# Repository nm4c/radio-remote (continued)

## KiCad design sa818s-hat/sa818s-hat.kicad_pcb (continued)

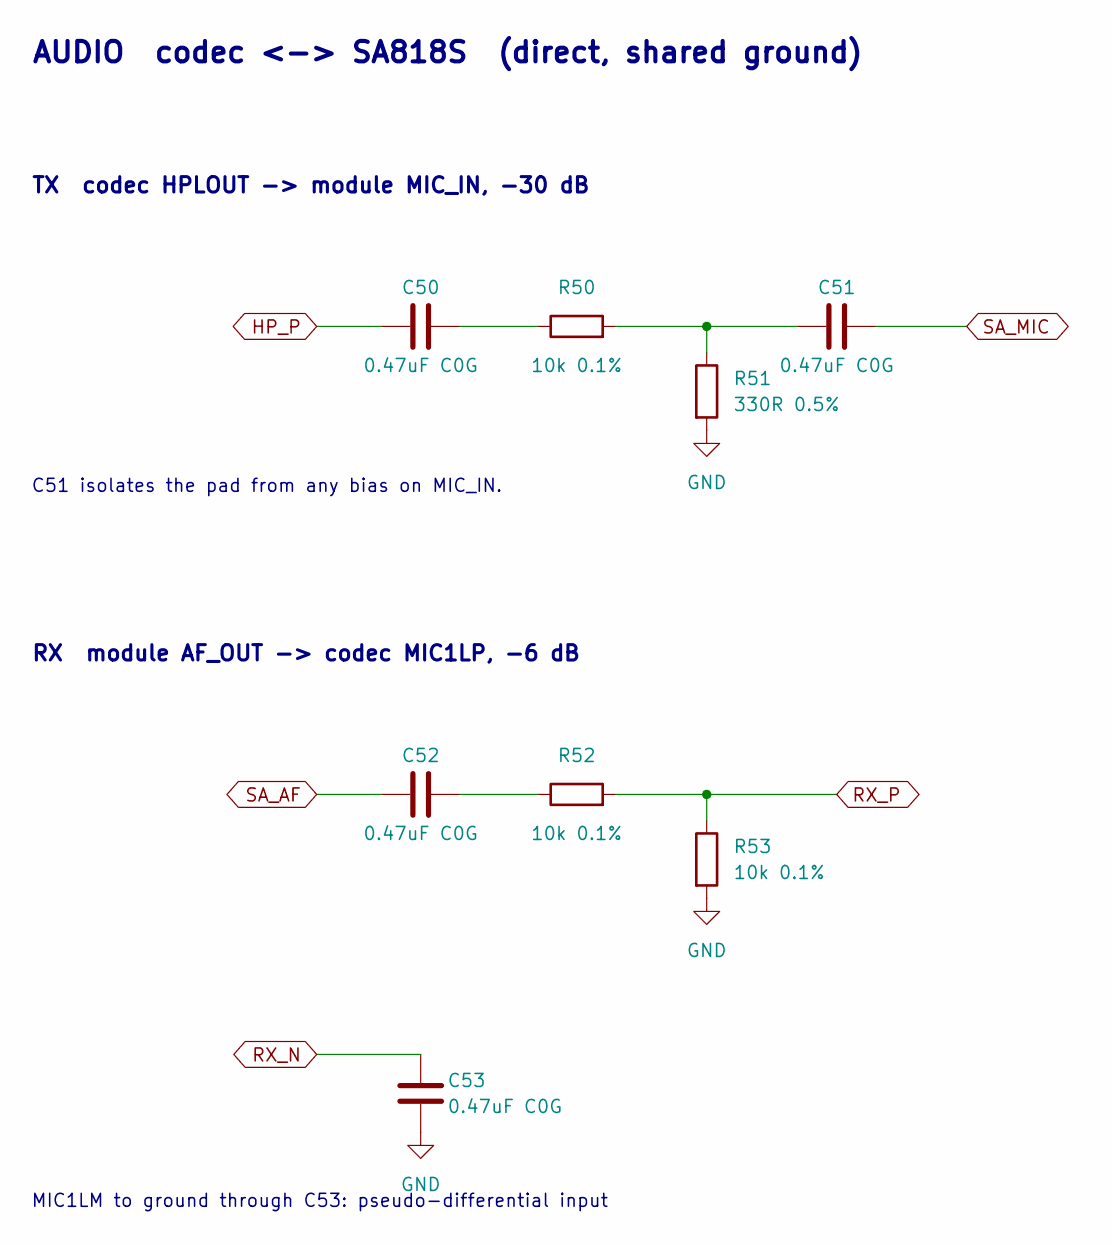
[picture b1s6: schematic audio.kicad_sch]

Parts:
C50, C51, C52, C53: 0.47uF C0G; C_1206_3216Metric; LCSC C6049896
R50, R52, R53: 10k 0.1%; R_0603_1608Metric; LCSC C95204
R51: 330R 0.5%; R_0603_1608Metric; LCSC C723588

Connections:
GND: C53.2, R51.2, R53.2; also elsewhere on the board
HP_P: C50.1; also elsewhere on the board
unnamed: C50.2, R50.1
unnamed: C51.1, R50.2, R51.1
unnamed: C52.2, R52.1
RX_N: C53.1; also elsewhere on the board
RX_P: R52.2, R53.1; also elsewhere on the board
SA_AF: C52.1; also elsewhere on the board
SA_MIC: C51.2; also elsewhere on the board

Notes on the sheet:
AUDIO codec <-> SA818S (direct, shared ground)
TX codec HPLOUT -> module MIC_IN, -30 dB
C51 isolates the pad from any bias on MIC_IN.
RX module AF_OUT -> codec MIC1LP, -6 dB
MIC1LM to ground through C53: pseudo-differential input

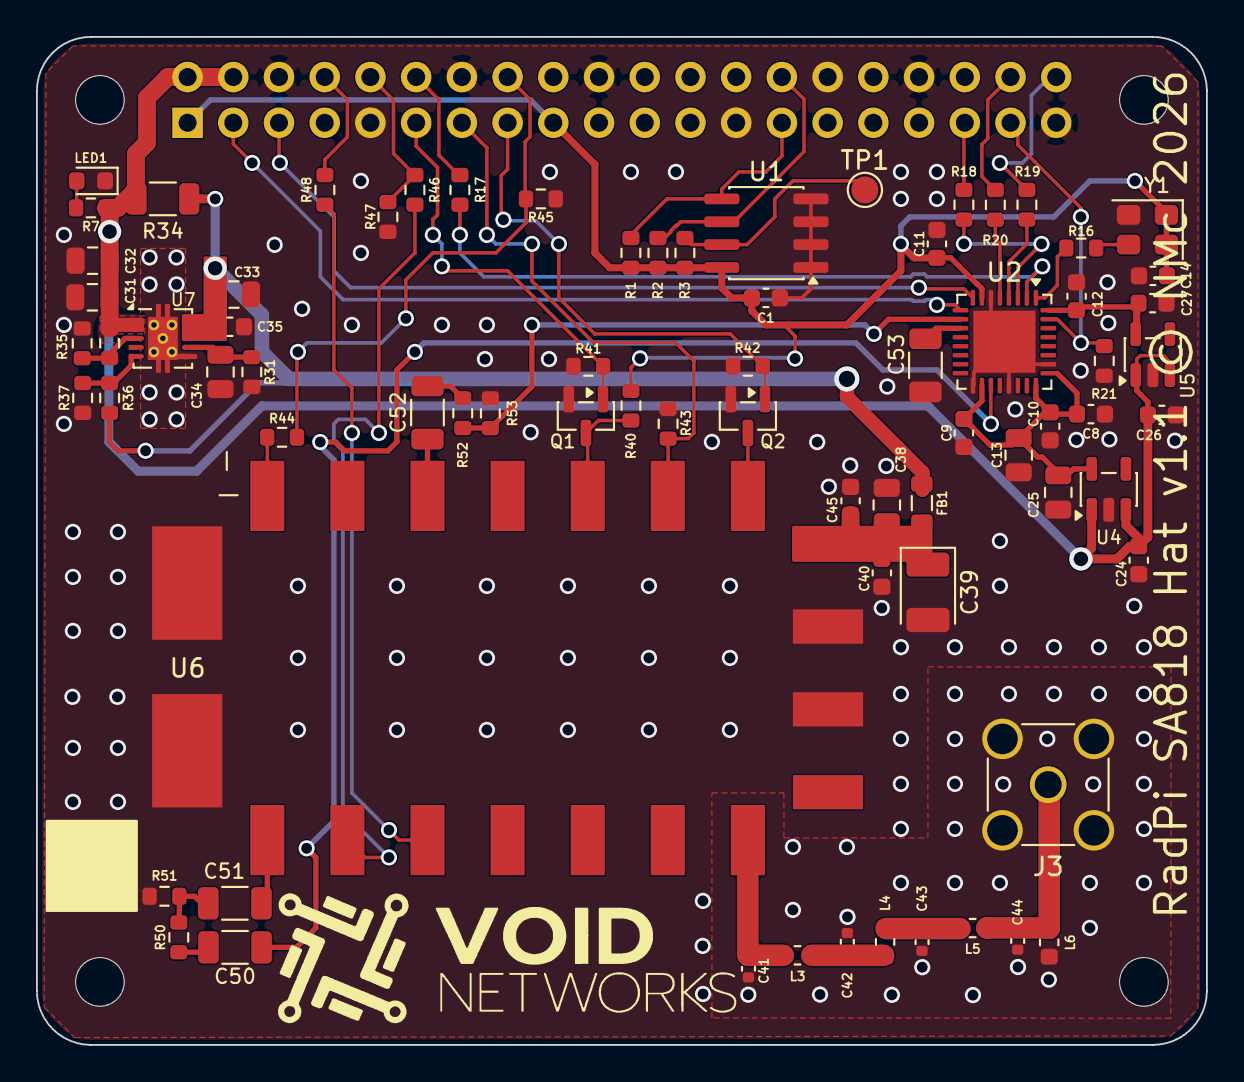
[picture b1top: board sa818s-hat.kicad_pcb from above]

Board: 2 copper layers, 65.0 x 56.0 mm, 80 parts (1 on the bottom side), 50 nets.

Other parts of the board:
MH1, MH2, MH3, MH4: MountingHole_2.7mm_M2.5

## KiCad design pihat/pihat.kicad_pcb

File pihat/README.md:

# RadPi Control HAT

A Raspberry Pi HAT that replaces the hand-wired interface in [`../docs/HARDWARE.md`](../docs/HARDWARE.md).
It has everything on one board:

- **Opto-isolated control:** PTT, channel UP/DOWN and BUSY through a TCMT4100.
- **On-board sound card:** a TLV320AIC3104 I2S codec, with isolation transformers to the radio's
  mic input and speaker.
- **Power:** a 13.8 V input with protection, and a 5 V buck that also powers the Pi.
- **HAT ID EEPROM:** tells the Pi which sound-card overlay to load at boot.

| File | What it is |
|---|---|
| `pihat.kicad_pro` / `.kicad_sch` / `.kicad_pcb` | KiCad project |
| [`docs/schematic/radpi-control-hat.html`](docs/schematic/radpi-control-hat.html) | Reference schematic: 7 sheets, netlist, parts, pre-layout checks. Open it in a browser. |
| [`docs/BOM.md`](docs/BOM.md) | BoM notes and cost summary |
| [`docs/jlc-bom.csv`](docs/jlc-bom.csv) | JLCPCB assembly BoM |
| `docs/schematic/gen.py` | Regenerates the schematic page and the CSV from one parts list |
| [`docs/schematic.svg`](docs/schematic.svg) | The KiCad schematic, all sheets on one page (made by `tools/kicad/overview.py`) |

## Schematic

The whole circuit on one page, straight from the KiCad schematic (click to open it full size; part
and net names are searchable). Labels with the same name are connected. Regenerate it with
`python3 tools/kicad/overview.py` after changing the schematic.

## Software

The codec uses the `tlv320aic3x` driver already in Raspberry Pi OS, with a small custom overlay
(still to write): `simple-audio-card` with the codec at I2C 0x18, `reset-gpios` on GPIO26 (active
low) and a fixed 12 MHz system clock. `simple-audio-card` always clocks the codec from MCLK, which
is where Y1's 12 MHz goes on this board. Don't use the stock `dacberry400` overlay: its driver
clocks the codec's PLL from BCLK while telling it the clock is 12 MHz, so the sample rate would be
wrong here. In ALSA, set the HPLCOM output to "differential of HPLOUT" so T1 is driven
differentially. After that the remote-head server sees an ordinary ALSA sound card: set
`audio.input_device` / `output_device` in `config.yaml` to its name, and `gpio.busy_pin: 23` with
`busy_pull_up: true`.

**Powering:** the HAT powers the Pi through header pins 2 and 4. Don't power the Pi from its USB-C
socket while the HAT is fitted and its 13.8 V input is off: the Pi's 5 V would then sit on the
buck's output with no input, which the LMR33640 datasheet says not to allow.

## Licence

The hardware design in this folder is licensed under the **CERN Open Hardware Licence v2, Strongly
Reciprocal (CERN-OHL-S-2.0)**. See [`LICENSE`](LICENSE). The generator scripts in `tools/` and
`docs/schematic/gen.py` are software and are GPL-3.0-or-later (see the repository root).

CERN-OHL-S asks that products made from the design say where the source can be found. Put this on
the board's silkscreen during layout, for example:

    RadPi Control HAT  CERN-OHL-S-2.0  github.com/nm4c/radpi

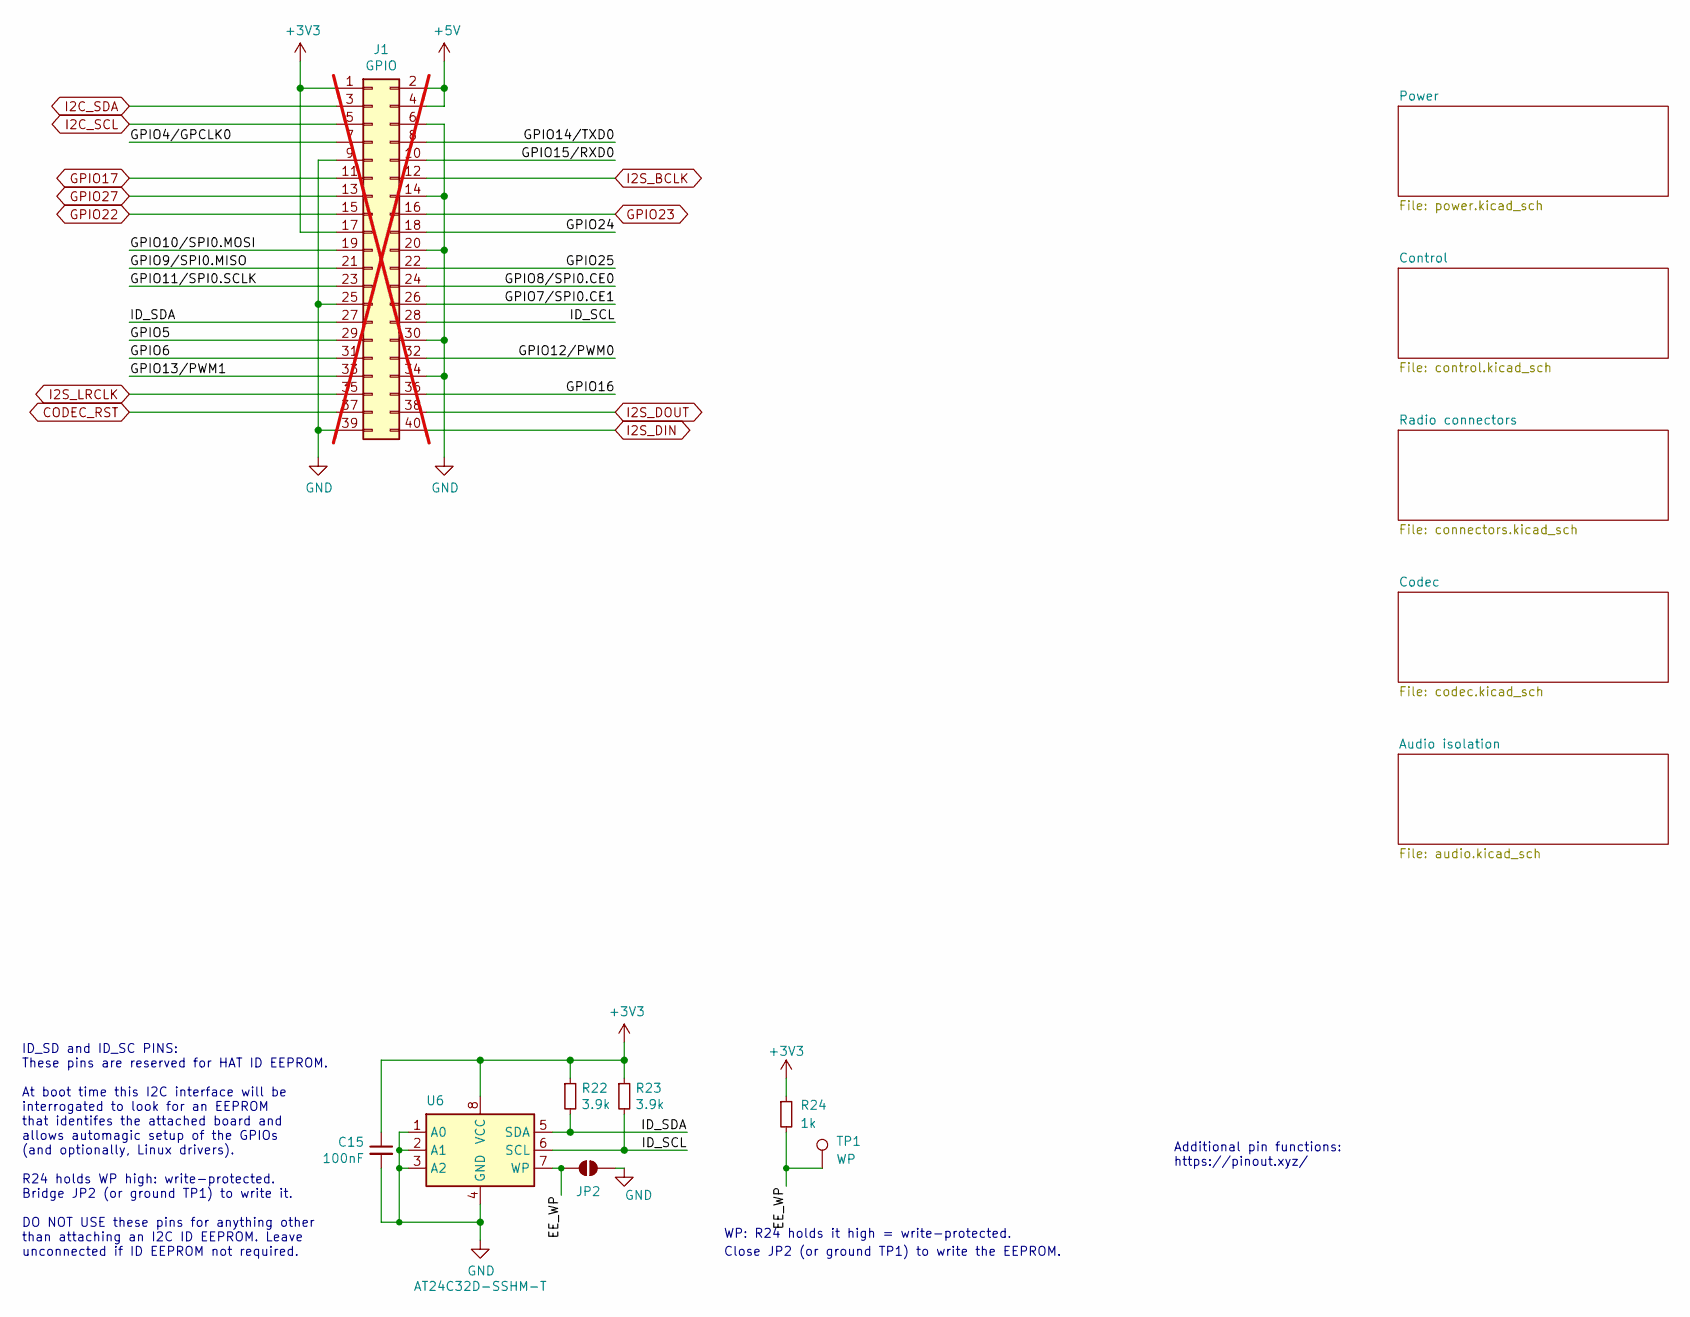
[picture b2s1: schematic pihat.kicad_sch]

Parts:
C15: 100nF; C_0603_1608Metric; LCSC C14663
J1: GPIO; PinSocket_2x20_P2.54mm_Vertical; LCSC C2977589; not fitted
JP2: WP write enable; SolderJumper-2_P1.3mm_Open_RoundedPad1.0x1.5mm
R22, R23: 3.9k; R_0603_1608Metric; LCSC C23018
R24: 1k; R_0603_1608Metric; LCSC C21190
TP1: WP; TestPoint_Pad_D1.5mm
U6: AT24C32D-SSHM-T; SOIC-8_3.9x4.9mm_P1.27mm; LCSC C60583

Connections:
+3V3: C15.1, J1.1, J1.17, R22.1, R23.1, R24.1, U6.8 (VCC); also elsewhere on the board
+5V: J1.2, J1.4; also elsewhere on the board
/EE_WP: JP2.1 (A), R24.2, TP1.1 (1_1), U6.7 (WP)
/GPIO4/GPCLK0: J1.7
/GPIO5: J1.29
/GPIO6: J1.31
/GPIO7/SPI0.CE1: J1.26
/GPIO8/SPI0.CE0: J1.24
/GPIO9/SPI0.MISO: J1.21
/GPIO10/SPI0.MOSI: J1.19
/GPIO11/SPI0.SCLK: J1.23
/GPIO12/PWM0: J1.32
/GPIO13/PWM1: J1.33
/GPIO14/TXD0: J1.8
/GPIO15/RXD0: J1.10
/GPIO16: J1.36
/GPIO24: J1.18
/GPIO25: J1.22
/ID_SCL: J1.28, R23.2, U6.6 (SCL)
/ID_SDA: J1.27, R22.2, U6.5 (SDA)
CODEC_RST: J1.37; also elsewhere on the board
GND: C15.2, J1.6, J1.9, J1.14, J1.20, J1.25, J1.30, J1.34, J1.39, JP2.2 (B), U6.1 (A0), U6.2 (A1), U6.3 (A2), U6.4 (GND); also elsewhere on the board
GPIO17: J1.11; also elsewhere on the board
GPIO22: J1.15; also elsewhere on the board
GPIO23: J1.16; also elsewhere on the board
GPIO27: J1.13; also elsewhere on the board
I2C_SCL: J1.5; also elsewhere on the board
I2C_SDA: J1.3; also elsewhere on the board
I2S_BCLK: J1.12; also elsewhere on the board
I2S_DIN: J1.40; also elsewhere on the board
I2S_DOUT: J1.38; also elsewhere on the board
I2S_LRCLK: J1.35; also elsewhere on the board

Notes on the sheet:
Additional pin functions: https://pinout.xyz/
ID_SD and ID_SC PINS: These pins are reserved for HAT ID EEPROM. At boot time this I2C interface will be interrogated to look for an EEPROM that identifes the attached board and allows automagic setup of the GPIOs (and optionally, Linux drivers). R24 holds WP high: write-protected. Bridge JP2 (or g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
WP: R24 holds it high = write-protected.
Close JP2 (or ground TP1) to write the EEPROM.

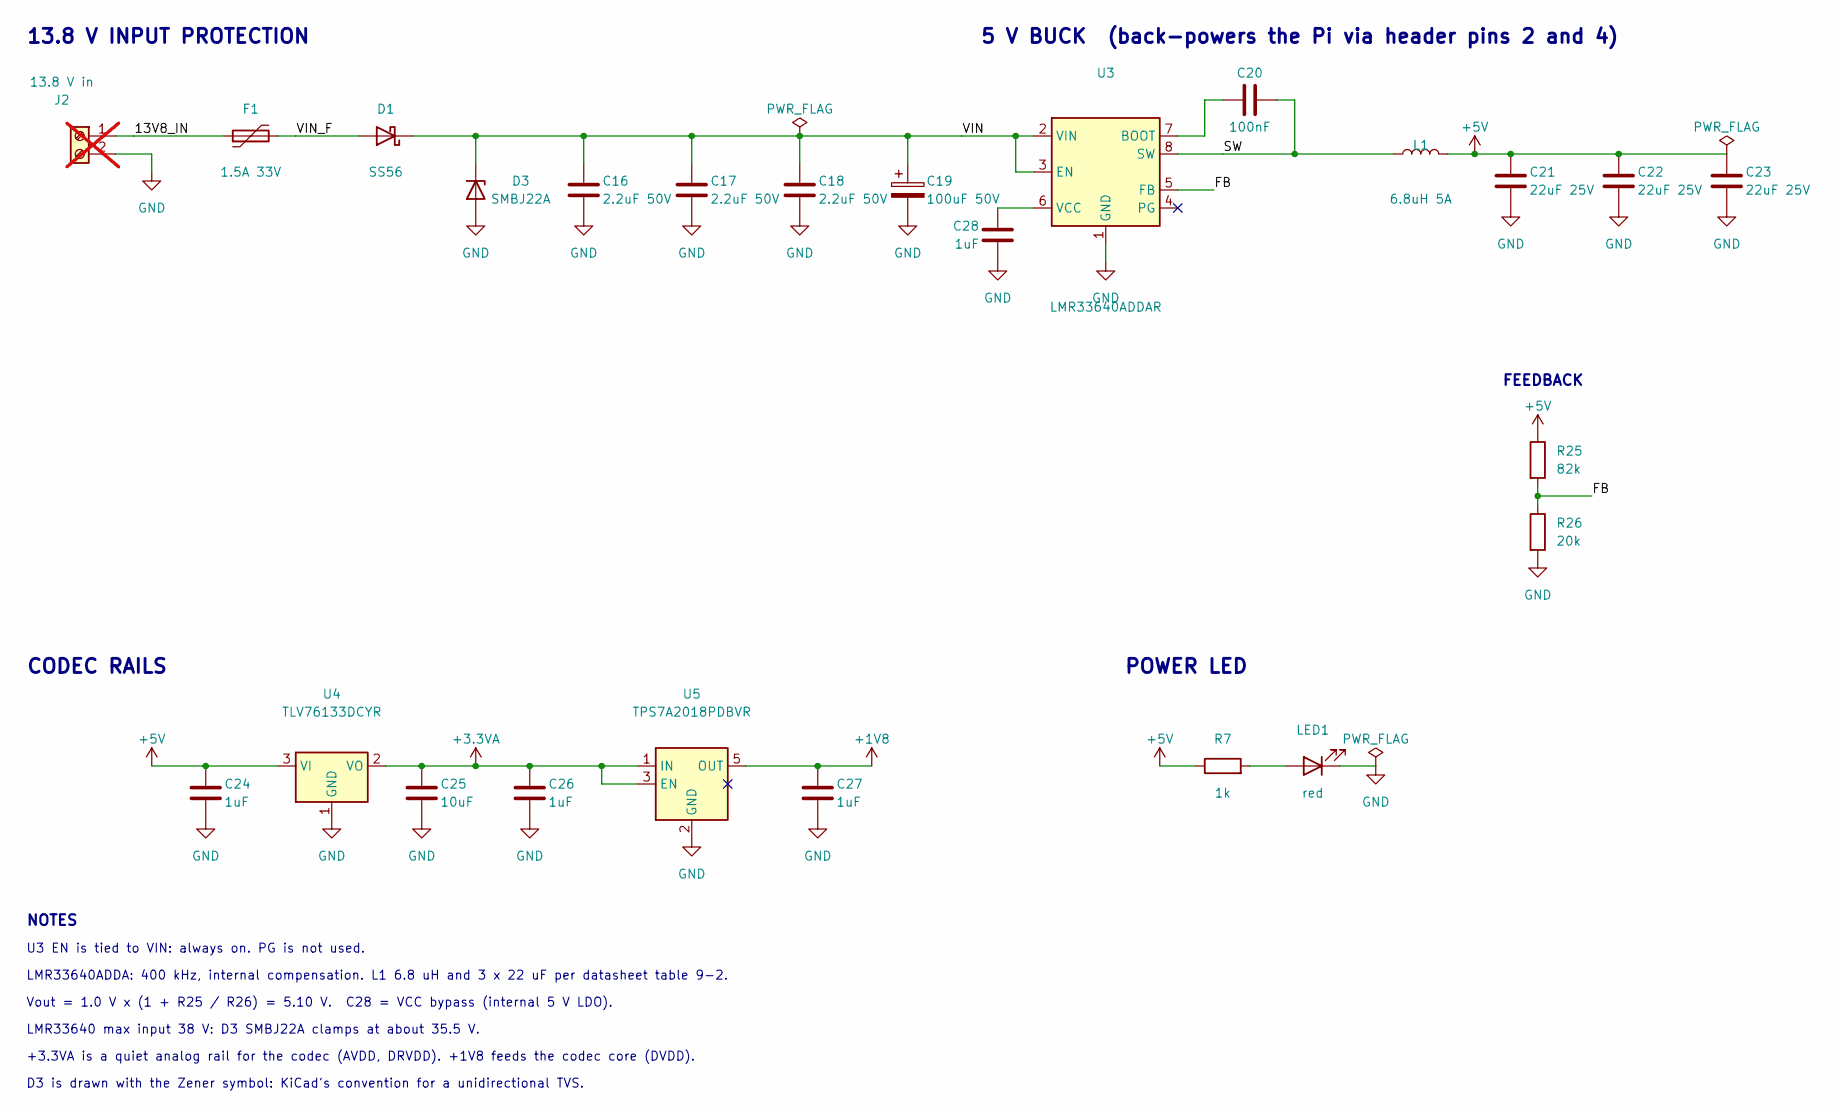
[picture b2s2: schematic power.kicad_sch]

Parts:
C16, C17, C18: 2.2uF 50V; C_1206_3216Metric; LCSC C50254
C19: 100uF 50V; CP_Elec_8x10.5; LCSC C72480
C20: 100nF; C_0603_1608Metric; LCSC C14663
C21, C22, C23: 22uF 25V; C_1206_3216Metric; LCSC C12891
C24, C26, C27, C28: 1uF; C_0603_1608Metric; LCSC C15849
C25: 10uF; C_0805_2012Metric; LCSC C15850
D1: SS56; D_SMA; LCSC C65009
D3: SMBJ22A; D_SMB; LCSC C224015
F1: 1.5A 33V; Fuse_1812_4532Metric; LCSC C18198333
J2: 13.8 V in; Xinlaiya_XY2500V-F-3.5_1x02_P3.50mm_Vertical; LCSC C880554; not fitted
L1: 6.8uH 5A; L_Changjiang_FXL0630; LCSC C167221
LED1: red; LED_0603_1608Metric; LCSC C2286
R7: 1k; R_0603_1608Metric; LCSC C21190
R25: 82k; R_0603_1608Metric; LCSC C23254
R26: 20k; R_0603_1608Metric; LCSC C4184
U3: LMR33640ADDAR; Texas_HSOP-8-1EP_3.9x4.9mm_P1.27mm_ThermalVias; LCSC C2836966
U4: TLV76133DCYR; SOT-223-3_TabPin2; LCSC C7527500
U5: TPS7A2018PDBVR; SOT-23-5; LCSC C963430

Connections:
+1V8: C27.1, U5.5 (OUT); also elsewhere on the board
+3.3VA: C25.1, C26.1, U4.2 (VO), U5.1 (IN), U5.3 (EN); also elsewhere on the board
+5V: C21.1, C22.1, C23.1, C24.1, L1.2, R7.1, R25.1, U4.3 (VI); also elsewhere on the board
/Power/13V8_IN: F1.1, J2.1
/Power/FB: R25.2, R26.1, U3.5 (FB)
/Power/SW: C20.2, L1.1, U3.8 (SW)
/Power/VIN: C16.1, C17.1, C18.1, C19.1, D1.1 (K), D3.1 (K), U3.2 (VIN), U3.3 (EN)
/Power/VIN_F: D1.2 (A), F1.2
GND: C16.2, C17.2, C18.2, C19.2, C21.2, C22.2, C23.2, C24.2, C25.2, C26.2, C27.2, C28.2, D3.2 (A), J2.2, LED1.1 (K), R26.2, U3.1 (GND), U3.9 (GND), U4.1 (GND), U5.2 (GND); also elsewhere on the board
unnamed: LED1.2 (A), R7.2
unnamed: C20.1, U3.7 (BOOT)
unnamed: C28.1, U3.6 (VCC)

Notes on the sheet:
13.8 V INPUT PROTECTION
5 V BUCK (back-powers the Pi via header pins 2 and 4)
FEEDBACK
CODEC RAILS
POWER LED
NOTES
U3 EN is tied to VIN: always on. PG is not used.
LMR33640ADDA: 400 kHz, internal compensation. L1 6.8 uH and 3 x 22 uF per datasheet table 9-2.
Vout = 1.0 V x (1 + R25 / R26) = 5.10 V. C28 = VCC bypass (internal 5 V LDO).
LMR33640 max input 38 V: D3 SMBJ22A clamps at about 35.5 V.
+3.3VA is a quiet analog rail for the codec (AVDD, DRVDD). +1V8 feeds the codec core (DVDD).
D3 is drawn with the Zener symbol: KiCad's convention for a unidirectional TVS.

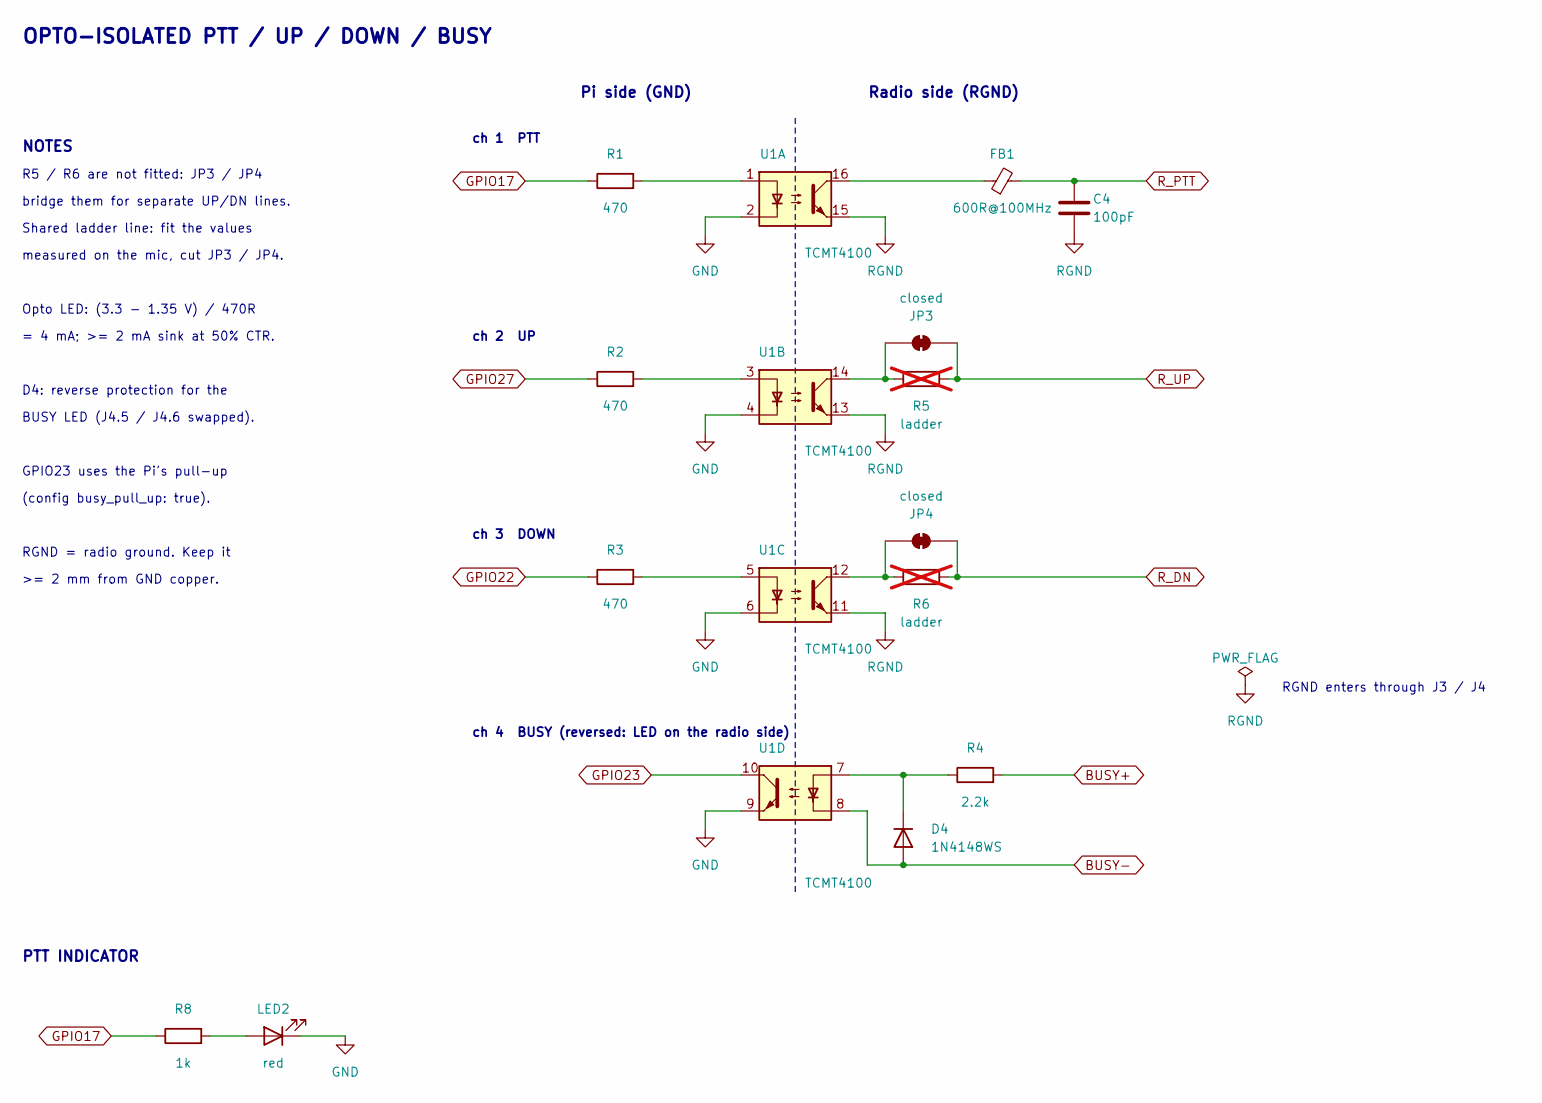
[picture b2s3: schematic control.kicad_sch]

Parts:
C4: 100pF; C_0603_1608Metric; LCSC C14858
D4: 1N4148WS; D_SOD-323; LCSC C2128
FB1: 600R@100MHz; L_0603_1608Metric; LCSC C1002
JP3, JP4: closed; SolderJumper-2_P1.3mm_Bridged_RoundedPad1.0x1.5mm
LED2: red; LED_0603_1608Metric; LCSC C2286
R1, R2, R3: 470; R_0603_1608Metric; LCSC C23179
R4: 2.2k; R_0603_1608Metric; LCSC C4190
R5, R6: ladder; R_0603_1608Metric; not fitted
R8: 1k; R_0603_1608Metric; LCSC C21190
U1: TCMT4100; SOP-16_4.4x10.4mm_P1.27mm; LCSC C2938669

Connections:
BUSY+: R4.2; also elsewhere on the board
BUSY-: D4.2 (A), U1.8; also elsewhere on the board
GND: LED2.1 (K), U1.2, U1.4, U1.6, U1.9; also elsewhere on the board
GPIO17: R1.1, R8.1; also elsewhere on the board
GPIO22: R3.1; also elsewhere on the board
GPIO23: U1.10; also elsewhere on the board
GPIO27: R2.1; also elsewhere on the board
unnamed: D4.1 (K), R4.1, U1.7
unnamed: FB1.1, U1.16
unnamed: JP3.1 (A), R5.1, U1.14
unnamed: JP4.1 (A), R6.1, U1.12
unnamed: LED2.2 (A), R8.2
unnamed: R1.2, U1.1
unnamed: R2.2, U1.3
unnamed: R3.2, U1.5
RGND: C4.2, U1.11, U1.13, U1.15; also elsewhere on the board
R_DN: JP4.2 (B), R6.2; also elsewhere on the board
R_PTT: C4.1, FB1.2; also elsewhere on the board
R_UP: JP3.2 (B), R5.2; also elsewhere on the board

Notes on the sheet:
OPTO-ISOLATED PTT / UP / DOWN / BUSY
Pi side (GND)
Radio side (RGND)
ch 1 PTT
ch 2 UP
ch 3 DOWN
ch 4 BUSY (reversed: LED on the radio side)
RGND enters through J3 / J4
PTT INDICATOR
NOTES
R5 / R6 are not fitted: JP3 / JP4
bridge them for separate UP/DN lines.
Shared ladder line: fit the values
measured on the mic, cut JP3 / JP4.
Opto LED: (3.3 - 1.35 V) / 470R
= 4 mA; >= 2 mA sink at 50% CTR.
D4: reverse protection for the
BUSY LED (J4.5 / J4.6 swapped).
GPIO23 uses the Pi's pull-up
(config busy_pull_up: true).
RGND = radio ground. Keep it
>= 2 mm from GND copper.

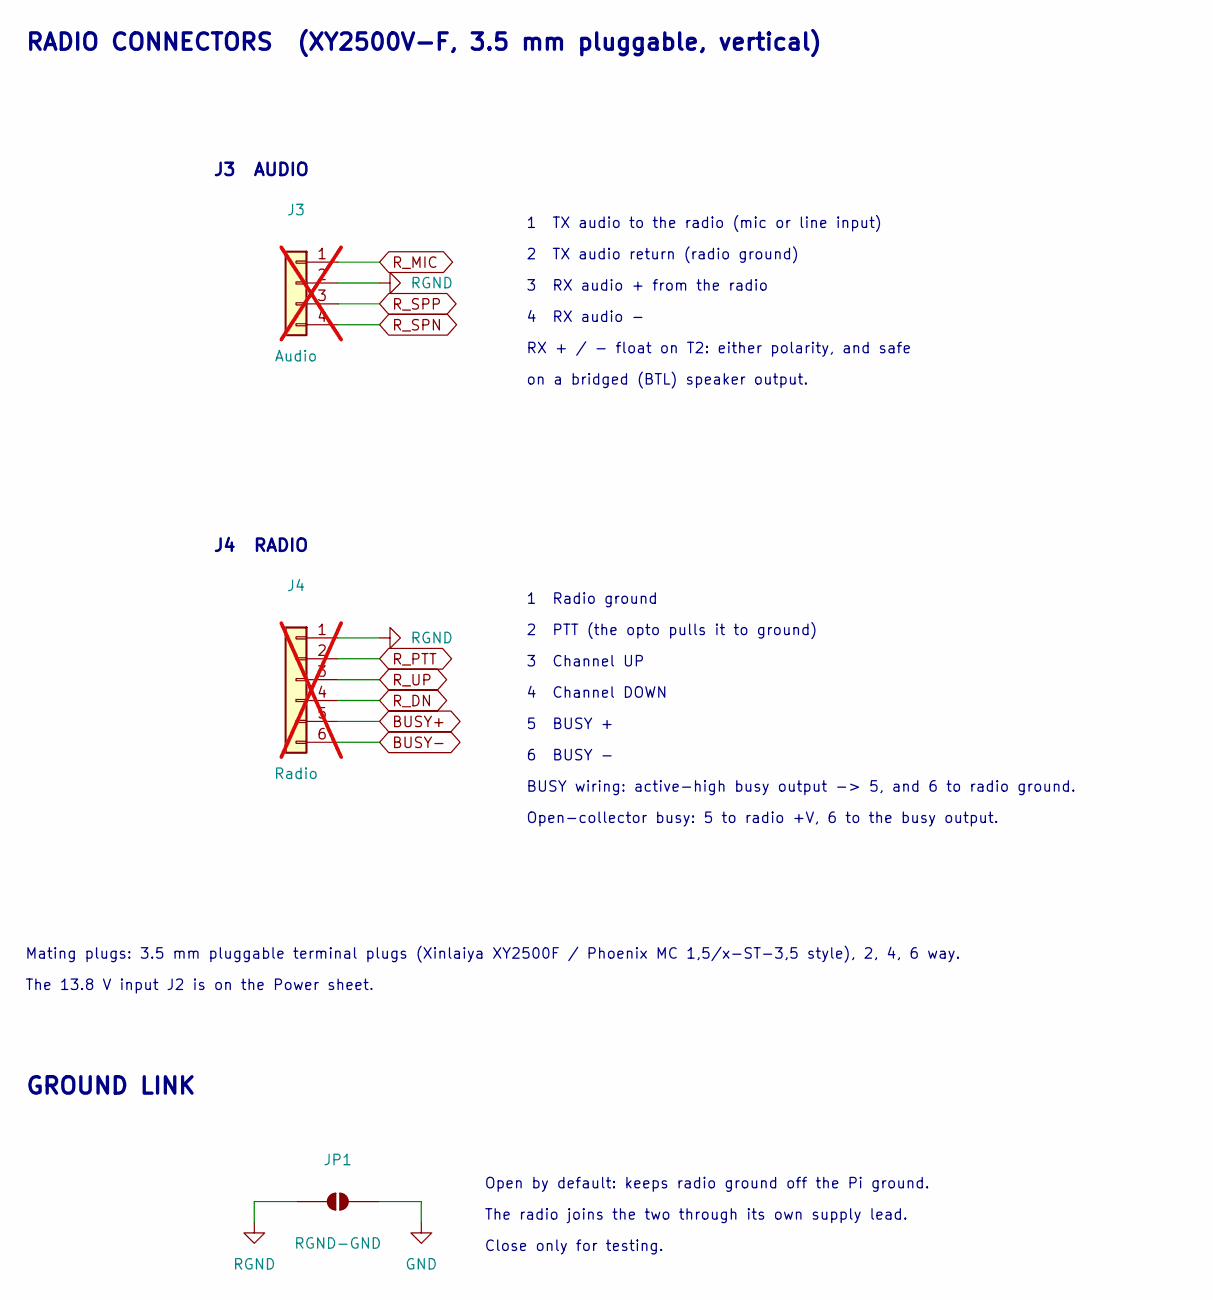
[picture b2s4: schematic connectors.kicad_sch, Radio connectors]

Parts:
J3: Audio; Xinlaiya_XY2500V-F-3.5_1x04_P3.50mm_Vertical; LCSC C880556; not fitted
J4: Radio; Xinlaiya_XY2500V-F-3.5_1x06_P3.50mm_Vertical; LCSC C880558; not fitted
JP1: RGND-GND; SolderJumper-2_P1.3mm_Open_RoundedPad1.0x1.5mm

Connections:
BUSY+: J4.5; also elsewhere on the board
BUSY-: J4.6; also elsewhere on the board
GND: JP1.2 (B); also elsewhere on the board
RGND: J3.2, J4.1, JP1.1 (A); also elsewhere on the board
R_DN: J4.4; also elsewhere on the board
R_MIC: J3.1; also elsewhere on the board
R_PTT: J4.2; also elsewhere on the board
R_SPN: J3.4; also elsewhere on the board
R_SPP: J3.3; also elsewhere on the board
R_UP: J4.3; also elsewhere on the board

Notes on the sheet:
RADIO CONNECTORS (XY2500V-F, 3.5 mm pluggable, vertical)
J3 AUDIO
1 TX audio to the radio (mic or line input)
2 TX audio return (radio ground)
3 RX audio + from the radio
4 RX audio -
RX + / - float on T2: either polarity, and safe
on a bridged (BTL) speaker output.
J4 RADIO
1 Radio ground
2 PTT (the opto pulls it to ground)
3 Channel UP
4 Channel DOWN
5 BUSY +
6 BUSY -
BUSY wiring: active-high busy output -> 5, and 6 to radio ground.
Open-collector busy: 5 to radio +V, 6 to the busy output.
Mating plugs: 3.5 mm pluggable terminal plugs (Xinlaiya XY2500F / Phoenix MC 1,5/x-ST-3,5 style), 2, 4, 6 way.
The 13.8 V input J2 is on the Power sheet.
GROUND LINK
Open by default: keeps radio ground off the Pi ground.
The radio joins the two through its own supply lead.
Close only for testing.

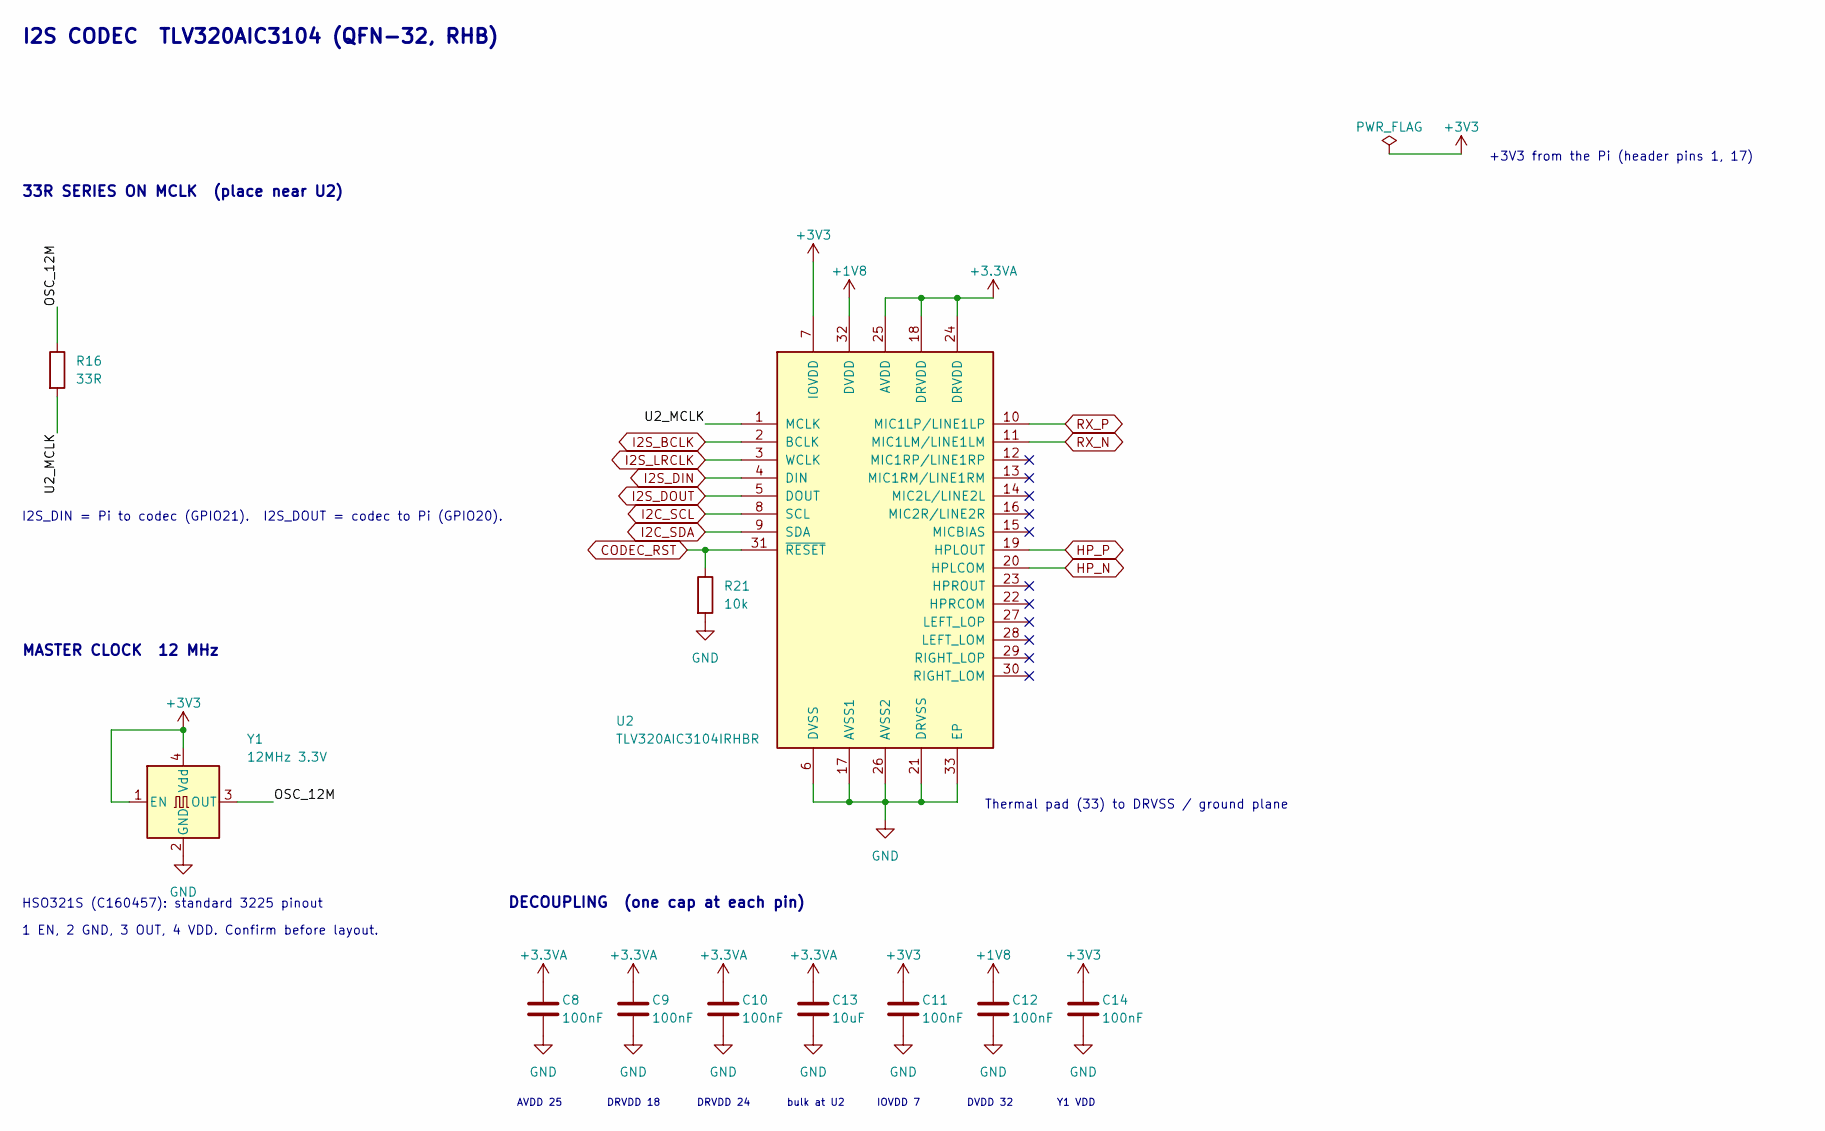
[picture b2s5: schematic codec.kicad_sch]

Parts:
C8, C9, C10, C11, C12, C14: 100nF; C_0603_1608Metric; LCSC C14663
C13: 10uF; C_0805_2012Metric; LCSC C15850
R16: 33R; R_0603_1608Metric; LCSC C23140
R21: 10k; R_0603_1608Metric; LCSC C25804
U2: TLV320AIC3104IRHBR; QFN-32-1EP_5x5mm_P0.5mm_EP3.45x3.45mm; LCSC C181753
Y1: 12MHz 3.3V; Oscillator_SMD_Abracon_ASE-4Pin_3.2x2.5mm; LCSC C160457

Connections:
+1V8: C12.1, U2.32 (DVDD); also elsewhere on the board
+3.3VA: C8.1, C9.1, C10.1, C13.1, U2.18 (DRVDD), U2.24 (DRVDD), U2.25 (AVDD); also elsewhere on the board
+3V3: C11.1, C14.1, U2.7 (IOVDD), Y1.1 (EN), Y1.4 (Vdd); also elsewhere on the board
/Codec/OSC_12M: R16.1, Y1.3 (OUT)
/Codec/U2_MCLK: R16.2, U2.1 (MCLK)
CODEC_RST: R21.1, U2.31 (~RESET); also elsewhere on the board
GND: C8.2, C9.2, C10.2, C11.2, C12.2, C13.2, C14.2, R21.2, U2.6 (DVSS), U2.17 (AVSS1), U2.21 (DRVSS), U2.26 (AVSS2), U2.33 (EP), Y1.2 (GND); also elsewhere on the board
HP_N: U2.20 (HPLCOM); also elsewhere on the board
HP_P: U2.19 (HPLOUT); also elsewhere on the board
I2C_SCL: U2.8 (SCL); also elsewhere on the board
I2C_SDA: U2.9 (SDA); also elsewhere on the board
I2S_BCLK: U2.2 (BCLK); also elsewhere on the board
I2S_DIN: U2.4 (DIN); also elsewhere on the board
I2S_DOUT: U2.5 (DOUT); also elsewhere on the board
I2S_LRCLK: U2.3 (WCLK); also elsewhere on the board
RX_N: U2.11 (MIC1LM/LINE1LM); also elsewhere on the board
RX_P: U2.10 (MIC1LP/LINE1LP); also elsewhere on the board

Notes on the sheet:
I2S CODEC TLV320AIC3104 (QFN-32, RHB)
Thermal pad (33) to DRVSS / ground plane
33R SERIES ON MCLK (place near U2)
I2S_DIN = Pi to codec (GPIO21). I2S_DOUT = codec to Pi (GPIO20).
MASTER CLOCK 12 MHz
HSO321S (C160457): standard 3225 pinout
1 EN, 2 GND, 3 OUT, 4 VDD. Confirm before layout.
DECOUPLING (one cap at each pin)
AVDD 25
DRVDD 18
DRVDD 24
bulk at U2
IOVDD 7
DVDD 32
Y1 VDD
+3V3 from the Pi (header pins 1, 17)

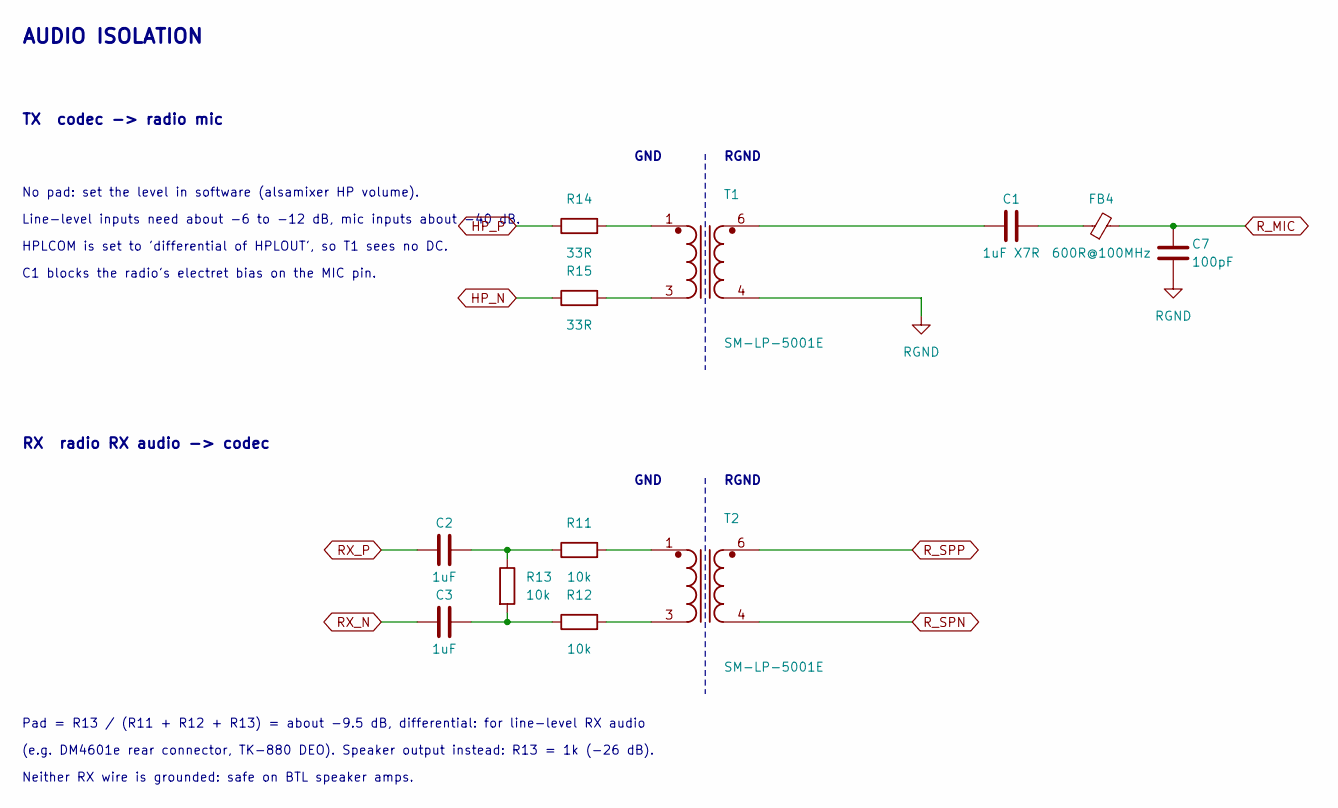
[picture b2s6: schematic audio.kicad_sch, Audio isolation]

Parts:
C1: 1uF X7R; C_0805_2012Metric; LCSC C28323
C2, C3: 1uF; C_0603_1608Metric; LCSC C15849
C7: 100pF; C_0603_1608Metric; LCSC C14858
FB4: 600R@100MHz; L_0603_1608Metric; LCSC C1002
R11, R12, R13: 10k; R_0603_1608Metric; LCSC C25804
R14, R15: 33R; R_0603_1608Metric; LCSC C23140
T1, T2: SM-LP-5001E; Bourns_SM-LP-5001; LCSC C840532

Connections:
HP_N: R15.1; also elsewhere on the board
HP_P: R14.1; also elsewhere on the board
unnamed: C1.1, T1.6
unnamed: C1.2, FB4.1
unnamed: C2.2, R11.1, R13.1
unnamed: C3.2, R12.1, R13.2
unnamed: R11.2, T2.1
unnamed: R12.2, T2.3
unnamed: R14.2, T1.1
unnamed: R15.2, T1.3
RGND: C7.2, T1.4; also elsewhere on the board
RX_N: C3.1; also elsewhere on the board
RX_P: C2.1; also elsewhere on the board
R_MIC: C7.1, FB4.2; also elsewhere on the board
R_SPN: T2.4; also elsewhere on the board
R_SPP: T2.6; also elsewhere on the board

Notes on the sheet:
AUDIO ISOLATION
TX codec -> radio mic
GND
RGND
No pad: set the level in software (alsamixer HP volume).
Line-level inputs need about -6 to -12 dB, mic inputs about -40 dB.
HPLCOM is set to 'differential of HPLOUT', so T1 sees no DC.
C1 blocks the radio's electret bias on the MIC pin.
RX radio RX audio -> codec
Pad = R13 / (R11 + R12 + R13) = about -9.5 dB, differential: for line-level RX audio
(e.g. DM4601e rear connector, TK-880 DEO). Speaker output instead: R13 = 1k (-26 dB).
Neither RX wire is grounded: safe on BTL speaker amps.

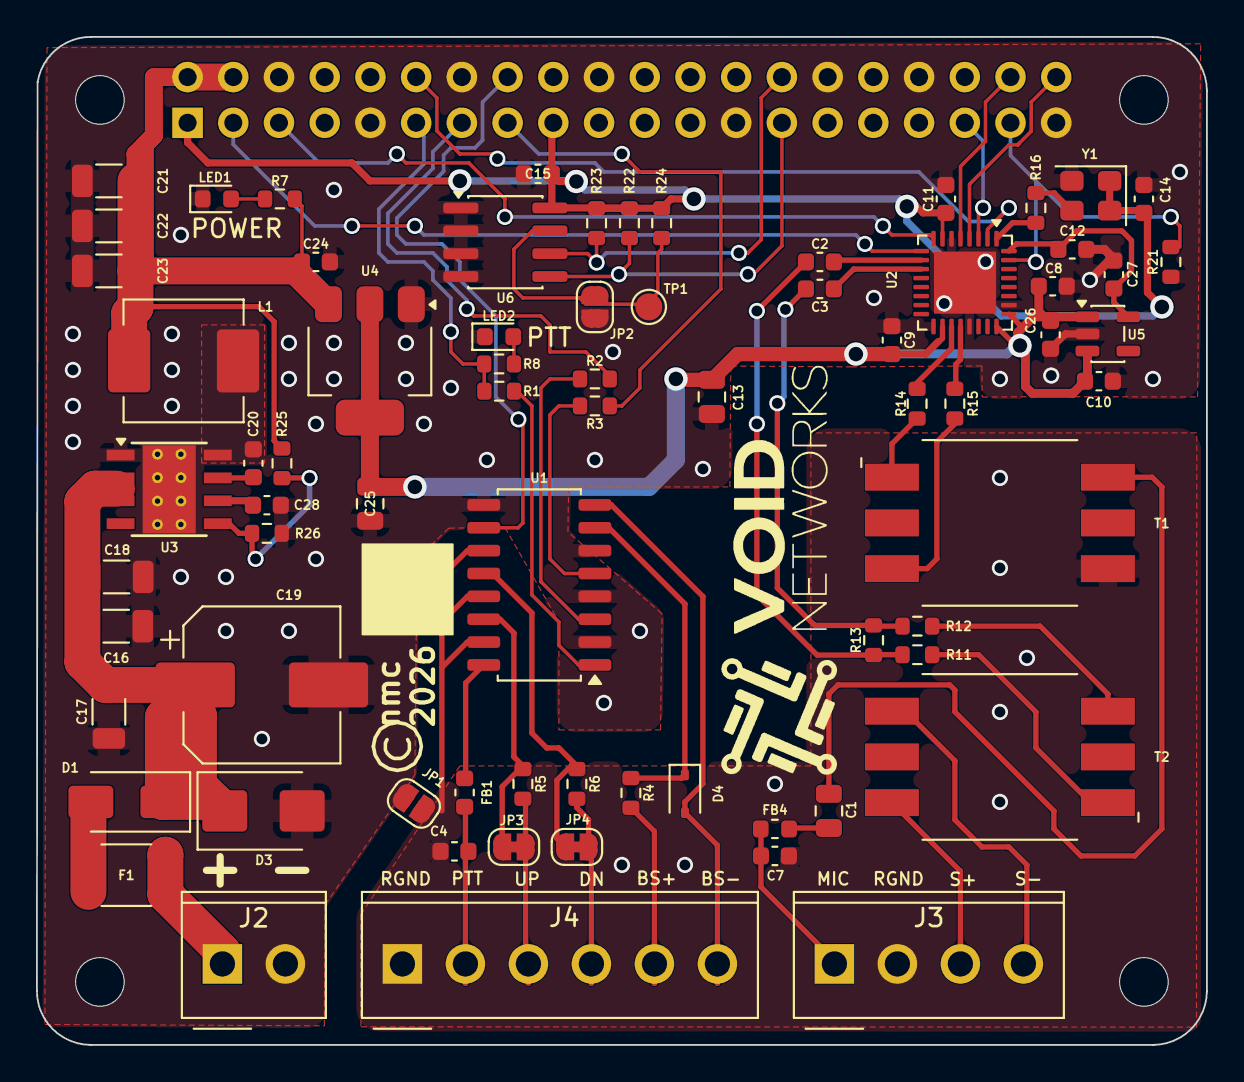
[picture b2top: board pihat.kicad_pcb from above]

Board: 2 copper layers, 65.0 x 56.0 mm, 77 parts (1 on the bottom side), 58 nets.

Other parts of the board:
MH1, MH2, MH3, MH4: MountingHole_2.7mm_M2.5

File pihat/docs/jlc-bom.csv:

Comment,Designator,Footprint,LCSC Part #
TCMT4100 quad opto,U1,SOIC-16_4.4x10.3mm_P1.27mm,C2938669
TLV320AIC3104IRHBR codec,U2,QFN-32-1EP_5x5mm_P0.5mm,C181753
LMR33640ADDAR buck,U3,HSOP-8-1EP_3.9x4.9mm_P1.27mm,C2836966
TLV76133DCYR 3.3 V LDO,U4,SOT-223-3_TabPin2,C7527500
TPS7A2018PDBVR 1.8 V LDO,U5,SOT-23-5,C963430
AT24C32D-SSHM-T EEPROM,U6,SOIC-8_3.9x4.9mm_P1.27mm,C60583
HSO321S 12 MHz 3.3 V oscillator,Y1,Oscillator_SMD_3225-4Pin,C160457
SM-LP-5001E 600:600 Ω transformer,"T1,T2",Bourns_SM-LP-5001,C840532
FXL0630-6R8-M 6.8 µH 5 A,L1,L_Changjiang_FXL0630,C167221
SS56 Schottky 60 V 5 A,D1,D_SMA,C65009
SMBJ22A TVS (Littelfuse),D3,D_SMB,C224015
1N4148WS,D4,D_SOD-323,C2128
1812L150/33GR PTC 1.5 A 33 V,F1,Fuse_1812,C18198333
KT-0603R red LED,"LED1,LED2",LED_0603,C2286
GZ1608D601TF ferrite 600 Ω,"FB1,FB4",L_0603,C1002
470 Ω 0603,"R1,R2,R3",R_0603,C23179
2.2 kΩ 0603,R4,R_0603,C4190
1 kΩ 0603,"R7,R8,R24",R_0603,C21190
10 kΩ 0603,"R11,R12,R13,R21",R_0603,C25804
33 Ω 0603,"R14,R15,R16",R_0603,C23140
3.9 kΩ 0603,"R22,R23",R_0603,C23018
82 kΩ 0603 1 %,R25,R_0603,C23254
20 kΩ 0603 1 %,R26,R_0603,C4184
1 µF 50 V X7R 0805,C1,C_0805,C28323
1 µF 50 V X5R 0603,"C2,C3,C24,C26,C27,C28",C_0603,C15849
100 pF C0G 0603,"C4,C7",C_0603,C14858
100 nF 50 V X7R 0603,"C8,C9,C10,C11,C12,C14,C15,C20",C_0603,C14663
10 µF 25 V X5R 0805,"C13,C25",C_0805,C15850
2.2 µF 50 V X7R 1206,"C16,C17,C18",C_1206,C50254
100 µF 50 V electrolytic 8×10.2,C19,CP_Elec_8x10.2,C72480
22 µF 25 V X5R 1206,"C21,C22,C23",C_1206,C12891
